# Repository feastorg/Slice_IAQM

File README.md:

# Industrial Air Quality Monitor

Industrial air quality monitor and alarm for BREAD.

## Introduction

[Short introduction on the project.]

## Usage

[Explain how to use the project. Include examples and screenshots if applicable.]

## Documentation

Please refer to the [docs](/docs) for more info.

---

<div align="center">
  
</div>

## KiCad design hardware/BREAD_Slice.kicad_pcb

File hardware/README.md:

## IAQM - Industrial Air Quality Monitor 

## Requirements

### Requirements List

- **Data Logging**
  - Logging of data to SD card
  - Real-time clock for accurate data logging

- **Feedback Alarms**
  - Visual feedback alarm
  - Auditory feedback alarm

- **Air Quality Readings**
  - Ambient temperature sensor
  - Ambient humidity sensor
  - Barometric pressure sensor
  - CO gas sensor
  - CH₄ gas sensor
  - NH₃ gas sensor
  - H₂S gas sensor
  - H₂ gas sensor
  - Smoke / flammable gas sensor
  - VOCs (Volatile Organic Compounds)
    - eCO2 readings
  - AQI (Air Quality Index)

### Component Table

| **Name**            | **Parameters Measured**                                         | **Value Abbreviation** | **Notes**                                                                                  |
|---------------------|-----------------------------------------------------------------|------------------------|-------------------------------------------------------------------------------------------|
| SD Card Reader      | Data Logging                                                    | N/A                    |                                                                                           |
| Real Time Clock     | Global Local Time                                               | N/A                    |                                                                                           |
| Piezo Buzzer        | Auditory Feedback                                               | N/A                    | For Alarm                                                                                      |
| Large LED           | Visual Feedback                                                 | N/A                    | For Alarm                                                                            |
| MQ-7                | Carbon Monoxide                                                 | CO                     | 10～500ppm, needs cycled coil heating.                                                                                |
| MQ-137              | Ammonia Gas                                                     | NH₃                    | 5～500ppm                                                                                  |
| MQ-8                | Hydrogen Gas                                                    | H₂                     | 100～1000ppm                                                                               |
| MQ-136              | Hydrogen Sulfide Gas                                            | H₂S                    | 1～200ppm                                                                                  |
| MQ-2                | Smoke / Combustible Gas                                          | N/A                    | 300～10000ppm (flammable gas)                                                             |
| MQ-3                | Alcohol Gas                                                     | C₂H₅OH                 | 25 ~ 500ppm (alcohol). Detects alcohol gases like a breathalyzer, not added in default build. |
| MQ-4                | Methane CNG Gas                                                 | CH₄                    | 300～10000ppm                                                                              |
| MQ-6                | Liquefied Petroleum Gas (LPG)                                   | C₃H₈                   | 300～10000ppm (propane). Not in default build.                                                                    |
| BME 280             | Ambient Temperature, Relative Humidity, Barometric Pressure     | N/A                    | Ambient Temp. -40 - +85 °C, Rel. Humidity 0 - 100 %, Baro. Pressure 300 - 1100 hPa                                 |
| ENS160              | Total Volatile Organic Compounds, Equivalent Carbon Dioxide, Air Quality Index | TVOC, eCO₂, AQI        | TVOC 0 – 65,000 ppb, eCO2 400 – 65,000ppm (CO₂ equiv.), AQI-UBA 1 to 5 |

### PV Box

| **Name**            | **Parameters Measured**                                         | **Value Abbreviation** | **Notes**                                                                                  |
|---------------------|-----------------------------------------------------------------|------------------------|-------------------------------------------------------------------------------------------|
| SD Card Reader      | Data Logging                                                    | N/A                    |                                                                                           |
| Real Time Clock     | Global Local Time                                               | N/A                    |                                                                                           |
| Piezo Buzzer        | Auditory Feedback                                               | N/A                    | For Alarm                                                                                      |
| Large LED           | Visual Feedback                                                 | N/A                    | For Alarm                                                                            |
| MQ-7                | Carbon Monoxide                                                 | CO                     | 10～500ppm, needs cycled coil heating.                                                                                |
| MQ-137              | Ammonia Gas                                                     | NH₃                    | 5～500ppm                                                                                  |
| MQ-8                | Hydrogen Gas                                                    | H₂                     | 100～1000ppm                                                                               |
| MQ-136              | Hydrogen Sulfide Gas                                            | H₂S                    | 1～200ppm                                                                                  |
| MQ-4                | Methane CNG Gas                                                 | CH₄                    | 300～10000ppm                                                                              |
| MQ-9B                | Carbon Monoxide & Methane CNG Gas                                                 | CO & CH₄                    | 10～500ppm CO, 300～10000ppm CH4                                                                              |
| BME 280             | Ambient Temperature, Relative Humidity, Barometric Pressure     | N/A                    | Ambient Temp. -40 - +85 °C, Rel. Humidity 0 - 100 %, Baro. Pressure 300 - 1100 hPa                                 |
| ENS160              | Total Volatile Organic Compounds, Equivalent Carbon Dioxide, Air Quality Index | TVOC, eCO₂, AQI        | TVOC 0 – 65,000 ppb, eCO2 400 – 65,000ppm (CO₂ equiv.), AQI-UBA 1 to 5 |

### Parts List

- SD conn: https://www.mouser.ca/ProductDetail/Molex/502570-0893?qs=xbccQsLEe0eiL%252BVgS3E4nA%3D%3D
- SD level shifter: https://www.mouser.ca/ProductDetail/Texas-Instruments/TXB0104D?qs=oFXvjAmG9Eh0u9dpGkn5zg%3D%3D
- batt holder: https://www.mouser.ca/ProductDetail/Keystone-Electronics/3000?qs=Mn60vILZNNbcLh3ZnzbtUw%3D%3D

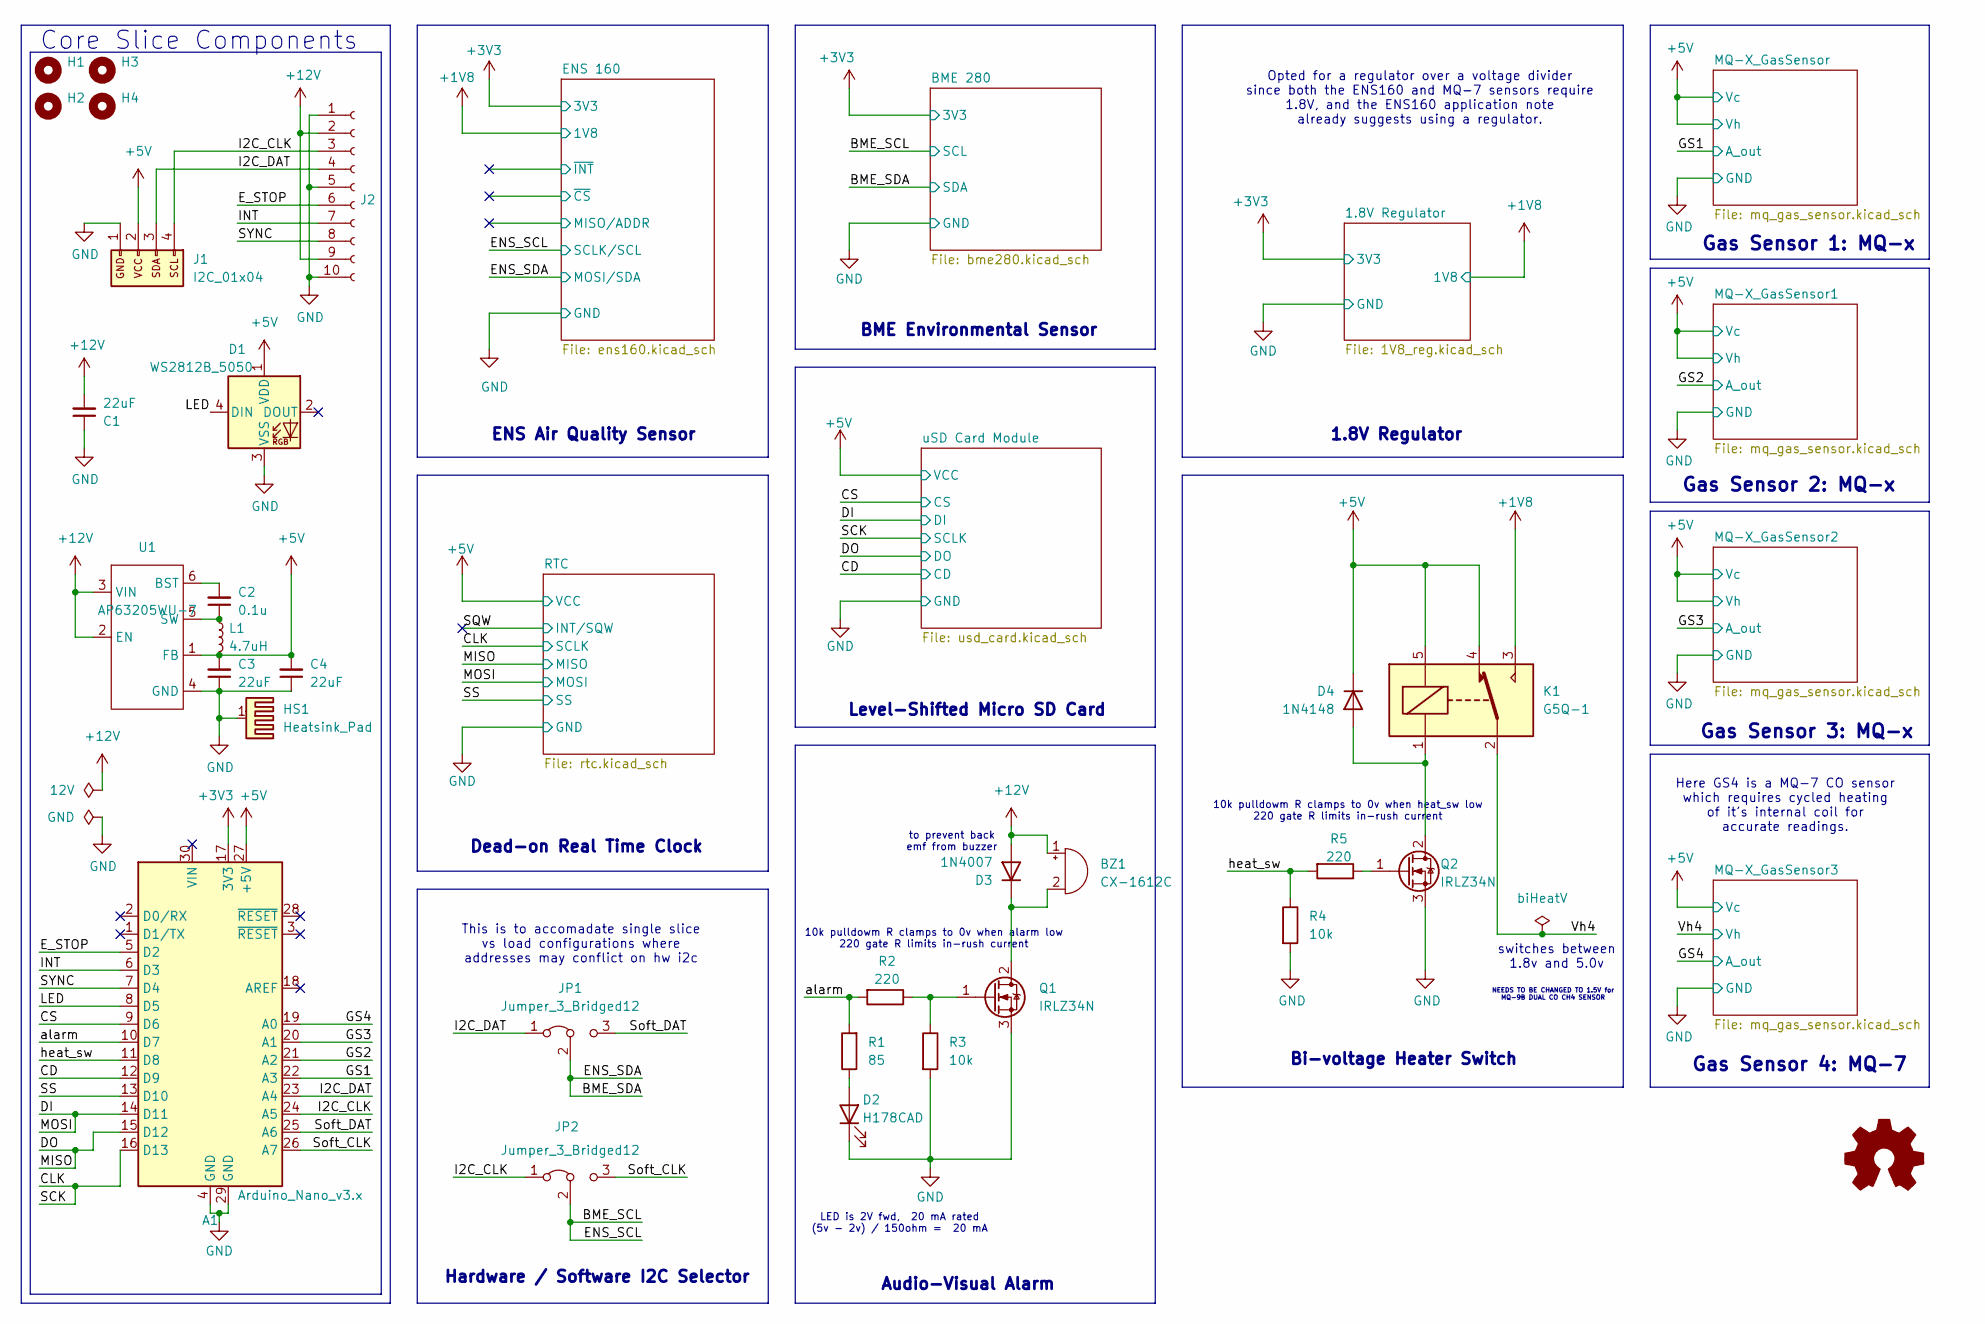
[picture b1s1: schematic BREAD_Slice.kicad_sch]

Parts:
A1: Arduino_Nano_v3.x; Arduino_Nano
BZ1: CX-1612C; Buzzer_15x7.5RM7.6
C1, C3, C4: 22uF; C_1206_3216Metric
C2: 0.1u; C_1206_3216Metric
D1: WS2812B_5050; WS2812-5050-4PIN
D2: H178CAD; H178CAD_P2.54mm_RightAngle_LED
D3: 1N4007; D_DO-35_SOD27_P7.62mm_Horizontal
D4: 1N4148; D_DO-35_SOD27_P7.62mm_Horizontal
H1, H2, H3, H4: MountingHole; MountingHole_5mm
HS1: Heatsink_Pad; Thermal_Pad
J1: I2C_01x04; JST_SH_SM04B-SRSS-TB_1x04-1MP_P1.00mm_Horizontal
J2: Conn_01x10_Female; PinSocket_1x10_P2.54mm_Horizontal
JP1, JP2: Jumper_3_Bridged12; SolderJumper-3_P1.3mm_Bridged2Bar12_Pad1.0x1.5mm_NumberLabe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
K1: G5Q-1; Relay_SPDT_Omron-G5Q-1
L1: 4.7uH; L_1210_3225Metric
Q1, Q2: IRLZ34N; TO-220-3_Horizontal_TabDown
R1: 85; R_1206_3216Metric_Pad1.30x1.75mm_HandSolder
R2, R5: 220; R_1206_3216Metric_Pad1.30x1.75mm_HandSolder
R3, R4: 10k; R_1206_3216Metric_Pad1.30x1.75mm_HandSolder
U1: AP63205WU-7; TSOT-23-6

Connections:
+1V8: K1.3; also elsewhere on the board
+3V3: A1.17 (3V3); also elsewhere on the board
+5V: A1.27 (+5V), C3.2, C4.2, D1.1 (VDD), D4.1 (K), J1.2, K1.4, K1.5, L1.2, U1.1 (FB); also elsewhere on the board
+12V: BZ1.1 (+), C1.2, D3.2 (A), J2.2, J2.9, U1.2 (EN), U1.3 (VIN)
/BME_SCL: JP2.2 (C); also elsewhere on the board
/BME_SDA: JP1.2 (C); also elsewhere on the board
/CD: A1.12 (D9); also elsewhere on the board
/CLK: A1.16 (D13); also elsewhere on the board
/CS: A1.9 (D6); also elsewhere on the board
/DI: A1.14 (D11); also elsewhere on the board
/DO: A1.15 (D12); also elsewhere on the board
/E_STOP: A1.5 (D2), J2.6
/GS1: A1.22 (A3); also elsewhere on the board
/GS2: A1.21 (A2); also elsewhere on the board
/GS3: A1.20 (A1); also elsewhere on the board
/GS4: A1.19 (A0); also elsewhere on the board
/I2C_CLK: A1.24 (A5), J1.4, J2.3, JP2.1 (A)
/I2C_DAT: A1.23 (A4), J1.3, J2.4, JP1.1 (A)
/INT: A1.6 (D3), J2.7
/LED: A1.8 (D5), D1.4 (DIN)
/SS: A1.13 (D10); also elsewhere on the board
/SYNC: A1.7 (D4), J2.8
/Soft_CLK: A1.26 (A7), JP2.3 (B)
/Soft_DAT: A1.25 (A6), JP1.3 (B)
/Vh4: K1.2; also elsewhere on the board
/alarm: A1.10 (D7), R1.2, R2.2
/heat_sw: A1.11 (D8), R4.1, R5.2
GND: A1.4 (GND), A1.29 (GND), C1.1, C3.1, C4.1, D1.3 (VSS), D2.1 (K), HS1.1, J1.1, J2.1, J2.5, J2.10, Q1.3 (S), Q2.3 (S), R3.2, R4.2, U1.4 (GND); also elsewhere on the board
unnamed: BZ1.2 (-), D3.1 (K), Q1.2 (D)
unnamed: D2.2 (A), R1.1
unnamed: D4.2 (A), K1.1, Q2.2 (D)
unnamed: Q1.1 (G), R2.1, R3.1
unnamed: Q2.1 (G), R5.1
unnamed: C2.2, U1.6 (BST)
unnamed: C2.1, L1.1, U1.5 (SW)

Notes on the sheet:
Gas Sensor 2: MQ-x
NEEDS TO BE CHANGED TO 1.5V for MQ-9B DUAL CO CH4 SENSOR
LED is 2V fwd, 20 mA rated (5v - 2v) / 150ohm = 20 mA
Gas Sensor 1: MQ-x
Bi-voltage Heater Switch
Gas Sensor 4: MQ-7
Gas Sensor 3: MQ-x
switches between 1.8v and 5.0v
1.8V Regulator
Level-Shifted Micro SD Card
Audio-Visual Alarm
Core Slice Components
BME Environmental Sensor
10k pulldowm R clamps to 0v when heat_sw low 220 gate R limits in-rush current
to prevent back emf from buzzer
10k pulldowm R clamps to 0v when alarm low 220 gate R limits in-rush current
Opted for a regulator over a voltage divider since both the ENS160 and MQ-7 sensors require 1.8V, and the ENS160 application note already suggests using a regulator.
ENS Air Quality Sensor
Dead-on Real Time Clock
This is to accomadate single slice vs load configurations where addresses may conflict on hw i2c
Here GS4 is a MQ-7 CO sensor which requires cycled heating of it's internal coil for accurate readings.
Hardware / Software I2C Selector

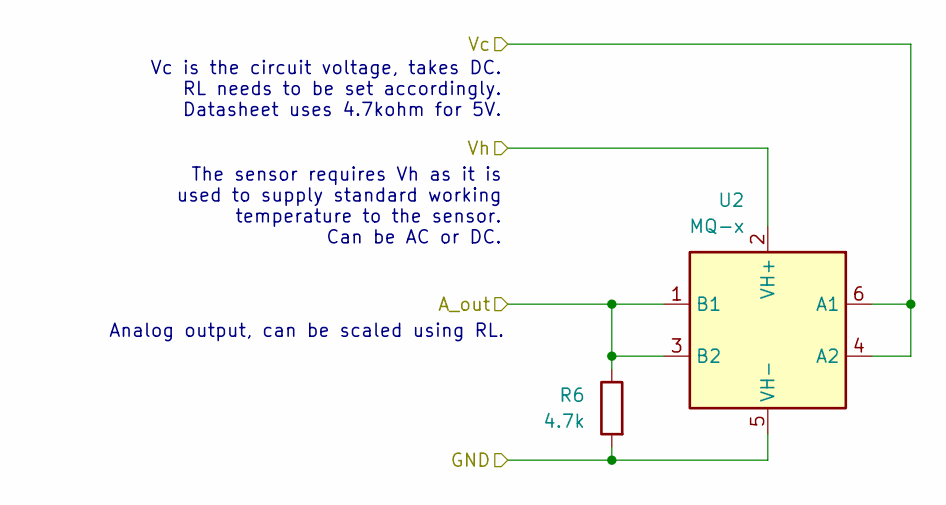
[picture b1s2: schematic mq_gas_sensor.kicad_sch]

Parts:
R6: 4.7k; R_1206_3216Metric_Pad1.30x1.75mm_HandSolder
U2: MQ-x; MQ-6

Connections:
+5V: U2.2 (VH+), U2.4 (A2), U2.6 (A1); also elsewhere on the board
/GS1: R6.1, U2.1 (B1), U2.3 (B2); also elsewhere on the board
GND: R6.2, U2.5 (VH-); also elsewhere on the board

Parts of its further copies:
R7, R8, R9: 4.7k; R_1206_3216Metric_Pad1.30x1.75mm_HandSolder
U3, U4, U5: MQ-x; MQ-6

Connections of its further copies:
+5V: U3.2 (VH+), U3.4 (A2), U3.6 (A1), U4.2 (VH+), U4.4 (A2), U4.6 (A1), U5.4 (A2), U5.6 (A1); also elsewhere on the board
/GS2: R7.1, U3.1 (B1), U3.3 (B2); also elsewhere on the board
/GS3: R8.1, U4.1 (B1), U4.3 (B2); also elsewhere on the board
/GS4: R9.1, U5.1 (B1), U5.3 (B2); also elsewhere on the board
/Vh4: U5.2 (VH+); also elsewhere on the board
GND: R7.2, R8.2, R9.2, U3.5 (VH-), U4.5 (VH-), U5.5 (VH-); also elsewhere on the board

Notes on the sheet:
The sensor requires Vh as it is used to supply standard working temperature to the sensor. Can be AC or DC.
Analog output, can be scaled using RL.
Vc is the circuit voltage, takes DC. RL needs to be set accordingly. Datasheet uses 4.7kohm for 5V.

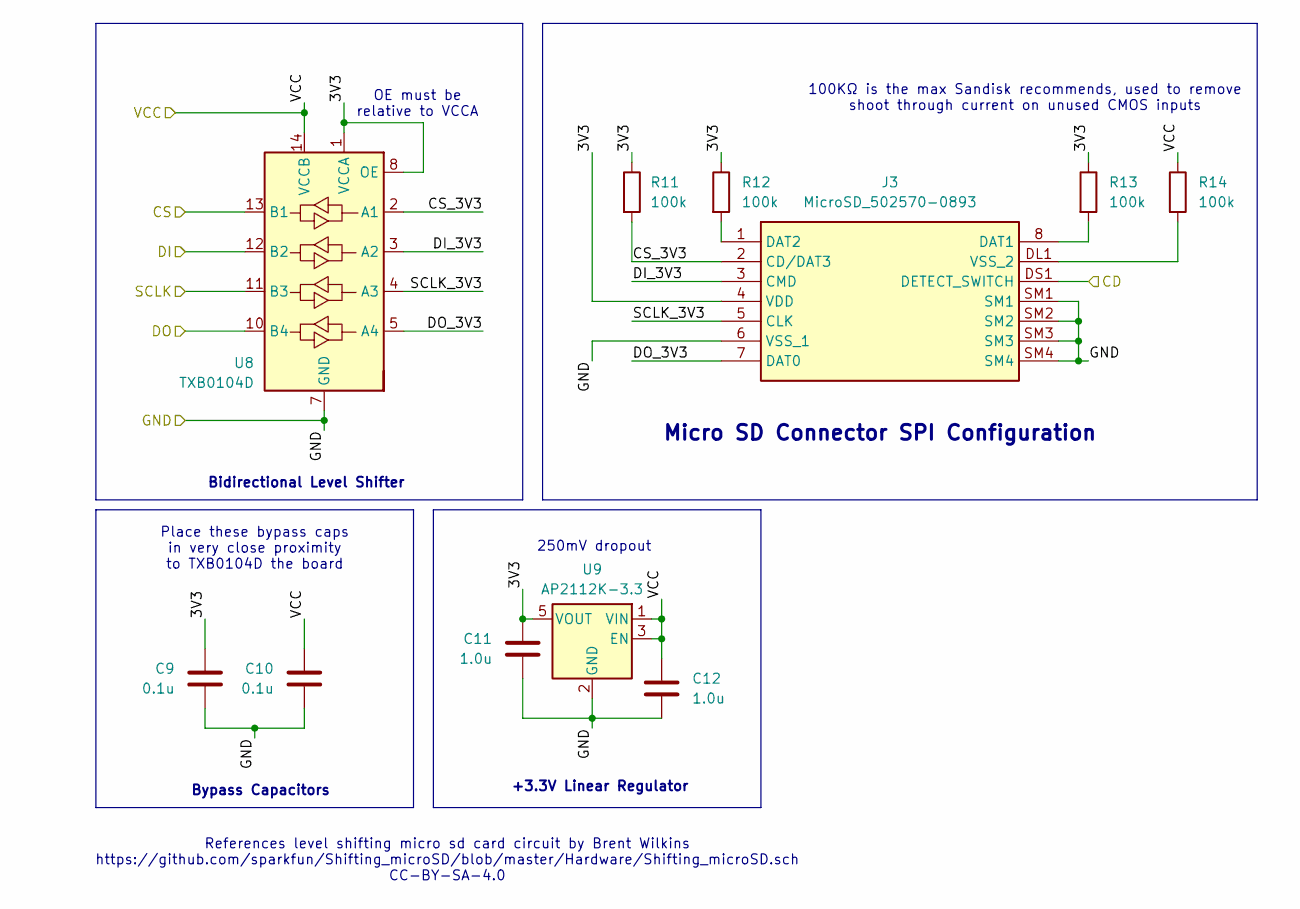
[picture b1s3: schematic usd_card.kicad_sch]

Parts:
C9, C10: 0.1u; C_1206_3216Metric_Pad1.33x1.80mm_HandSolder
C11, C12: 1.0u; C_1206_3216Metric_Pad1.33x1.80mm_HandSolder
J3: MicroSD_502570-0893; MicroSD_5025700893; Mouser Part Number 538-502570-0893
R11, R12, R13, R14: 100k; R_1206_3216Metric_Pad1.30x1.75mm_HandSolder
U8: TXB0104D; SOIC-14_3.9x8.7mm_P1.27mm
U9: AP2112K-3.3; SOT-23-5

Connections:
+5V: C10.1, C12.1, R14.1, U8.14 (VCCB), U9.1 (VIN), U9.3 (EN); also elsewhere on the board
/CD: J3.DS1 (DETECT_SWITCH); also elsewhere on the board
/CLK: U8.11 (B3); also elsewhere on the board
/CS: U8.13 (B1); also elsewhere on the board
/DI: U8.12 (B2); also elsewhere on the board
/DO: U8.10 (B4); also elsewhere on the board
/uSD Card Module/3V3: C9.1, C11.1, J3.4 (VDD), R11.1, R12.1, R13.1, U8.1 (VCCA), U8.8 (OE), U9.5 (VOUT)
/uSD Card Module/CS_3V3: J3.2 (CD/DAT3), R11.2, U8.2 (A1)
/uSD Card Module/DI_3V3: J3.3 (CMD), U8.3 (A2)
/uSD Card Module/DO_3V3: J3.7 (DAT0), U8.5 (A4)
/uSD Card Module/SCLK_3V3: J3.5 (CLK), U8.4 (A3)
GND: C9.2, C10.2, C11.2, C12.2, J3.6 (VSS_1), J3.SM1, J3.SM2, J3.SM3, J3.SM4, U8.7 (GND), U9.2 (GND); also elsewhere on the board
unnamed: J3.8 (DAT1), R13.2
unnamed: J3.1 (DAT2), R12.2
unnamed: J3.DL1 (VSS_2), R14.2

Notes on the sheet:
Bidirectional Level Shifter
Place these bypass caps in very close proximity to TXB0104D the board
+3.3V Linear Regulator
Micro SD Connector SPI Configuration
OE must be relative to VCCA
Bypass Capacitors
References level shifting micro sd card circuit by Brent Wilkins https://github.com/sparkfun/Shifting_microSD/blob/master/Hardware/Shifting_microSD.sch CC-BY-SA-4.0
100KΩ is the max Sandisk recommends, used to remove shoot through current on unused CMOS inputs
250mV dropout

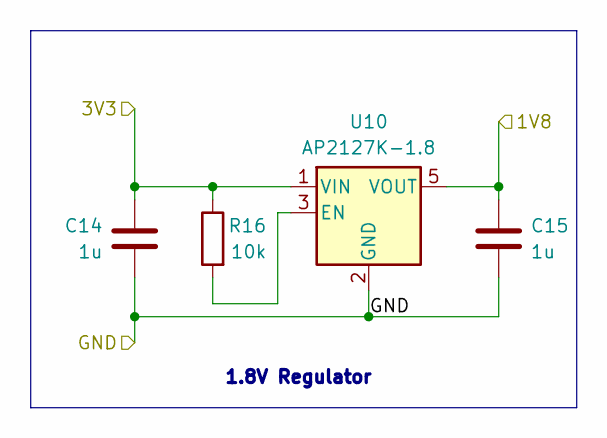
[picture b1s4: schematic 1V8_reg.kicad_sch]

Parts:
C14, C15: 1u; C_1206_3216Metric_Pad1.33x1.80mm_HandSolder
R16: 10k; R_1206_3216Metric_Pad1.30x1.75mm_HandSolder
U10: AP2127K-1.8; SOT-23-5

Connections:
+1V8: C15.1, U10.5 (VOUT); also elsewhere on the board
+3V3: C14.1, R16.1, U10.1 (VIN); also elsewhere on the board
GND: C14.2, C15.2, U10.2 (GND); also elsewhere on the board
unnamed: R16.2, U10.3 (EN)

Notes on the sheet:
1.8V Regulator

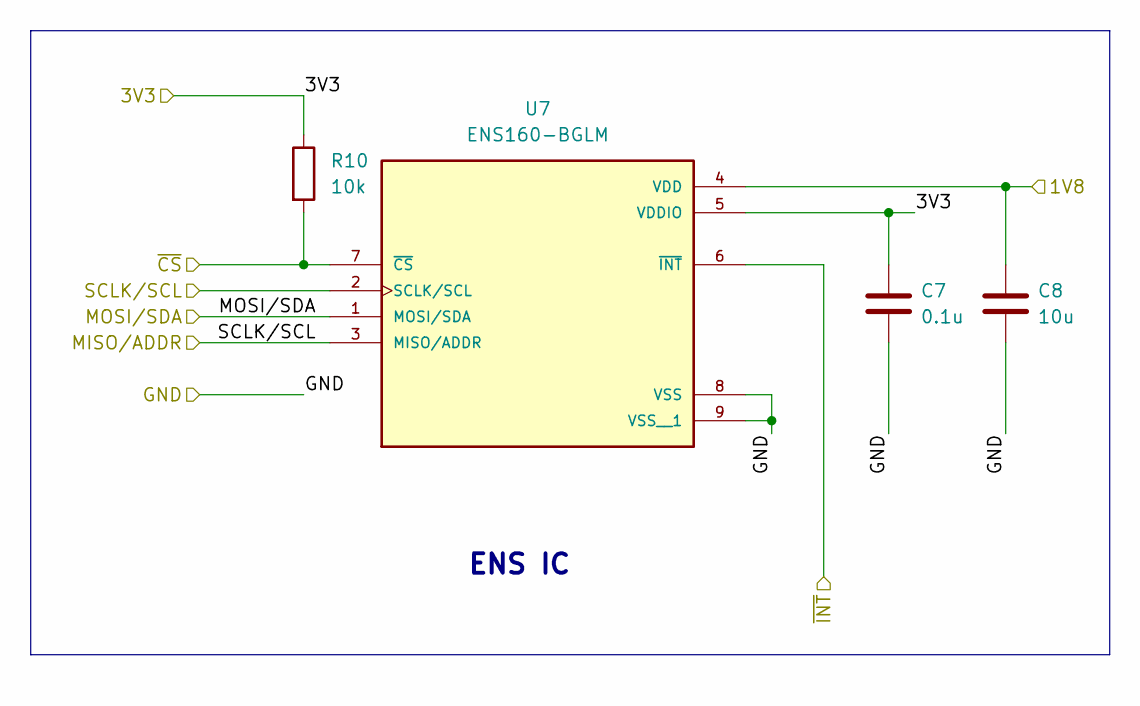
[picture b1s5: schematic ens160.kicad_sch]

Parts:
C7: 0.1u; C_1206_3216Metric_Pad1.33x1.80mm_HandSolder
C8: 10u; C_1206_3216Metric_Pad1.33x1.80mm_HandSolder
R10: 10k; R_1206_3216Metric_Pad1.30x1.75mm_HandSolder
U7: ENS160-BGLM; XDCR_ENS160-BGLM; PARTREV 1.3

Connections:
+1V8: C8.1, U7.4 (VDD); also elsewhere on the board
+3V3: C7.1, R10.1, U7.5 (VDDIO); also elsewhere on the board
/BME_SCL: U7.2 (SCLK/SCL), U7.3 (MISO/ADDR); also elsewhere on the board
/BME_SDA: U7.1 (MOSI/SDA); also elsewhere on the board
/ENS 160/~CS: R10.2, U7.7 (~CS)
/ENS 160/~INT: U7.6 (~INT)
GND: C7.2, C8.2, U7.8 (VSS), U7.9 (VSS__1); also elsewhere on the board

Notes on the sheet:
ENS IC

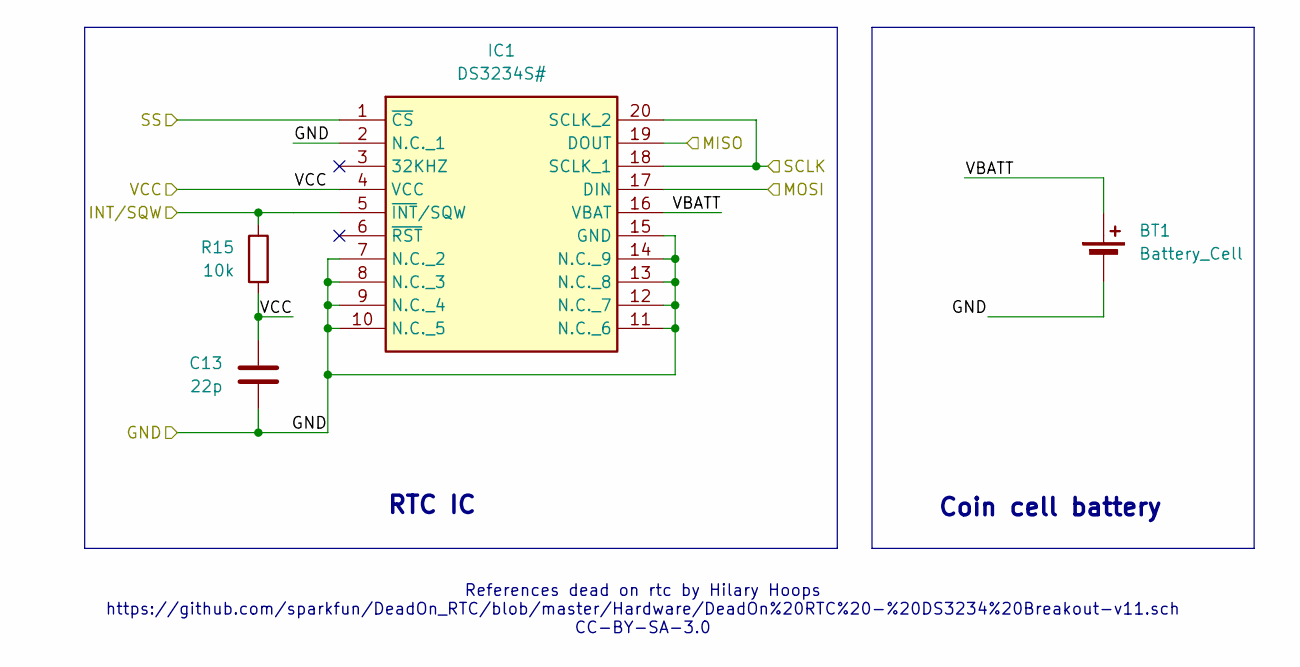
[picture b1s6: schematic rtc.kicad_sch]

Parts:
BT1: Battery_Cell; BatteryHolder_Keystone_3000_1x12mm
C13: 22p; C_1206_3216Metric_Pad1.33x1.80mm_HandSolder
IC1: DS3234S#; SOIC127P1032X265-20N; Mouser Part Number 700-DS3234S#
R15: 10k; R_1206_3216Metric_Pad1.30x1.75mm_HandSolder

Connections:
+5V: C13.1, IC1.4 (VCC), R15.2; also elsewhere on the board
/CLK: IC1.18 (SCLK_1), IC1.20 (SCLK_2); also elsewhere on the board
/DI: IC1.17 (DIN); also elsewhere on the board
/DO: IC1.19 (DOUT); also elsewhere on the board
/RTC/VBATT: BT1.1 (+), IC1.16 (VBAT)
/SQW: IC1.5 (~INT/SQW), R15.1
/SS: IC1.1 (~CS); also elsewhere on the board
GND: BT1.2 (-), C13.2, IC1.2 (N.C._1), IC1.7 (N.C._2), IC1.8 (N.C._3), IC1.9 (N.C._4), IC1.10 (N.C._5), IC1.11 (N.C._6), IC1.12 (N.C._7), IC1.13 (N.C._8), IC1.14 (N.C._9), IC1.15 (GND); also elsewhere on the board

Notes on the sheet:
References dead on rtc by Hilary Hoops https://github.com/sparkfun/DeadOn_RTC/blob/master/Hardware/DeadOn%20RTC%20-%20DS3234%20Breakout-v11.sch CC-BY-SA-3.0
RTC IC
Coin cell battery

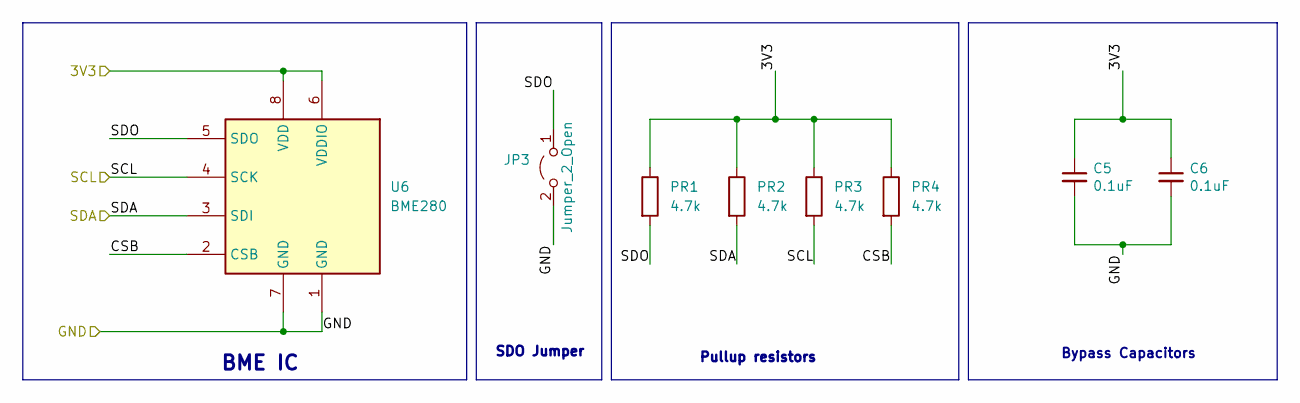
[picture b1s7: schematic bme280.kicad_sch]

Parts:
C5, C6: 0.1uF; C_0805_2012Metric
JP3: Jumper_2_Open; SolderJumper-2_P1.3mm_Open_TrianglePad1.0x1.5mm
PR1, PR2, PR3, PR4: 4.7k; R_1206_3216Metric_Pad1.30x1.75mm_HandSolder
U6: BME280; Bosch_LGA-8_2.5x2.5mm_P0.65mm_ClockwisePinNumbering

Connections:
+3V3: C5.1, C6.1, PR1.1, PR2.1, PR3.1, PR4.1, U6.6 (VDDIO), U6.8 (VDD); also elsewhere on the board
/BME 280/CSB: PR4.2, U6.2 (CSB)
/BME 280/SDO: JP3.1 (A), PR1.2, U6.5 (SDO)
/BME_SCL: PR3.2, U6.4 (SCK); also elsewhere on the board
/BME_SDA: PR2.2, U6.3 (SDI); also elsewhere on the board
GND: C5.2, C6.2, JP3.2 (B), U6.1 (GND), U6.7 (GND); also elsewhere on the board

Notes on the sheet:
Bypass Capacitors
SDO Jumper
BME IC
Pullup resistors

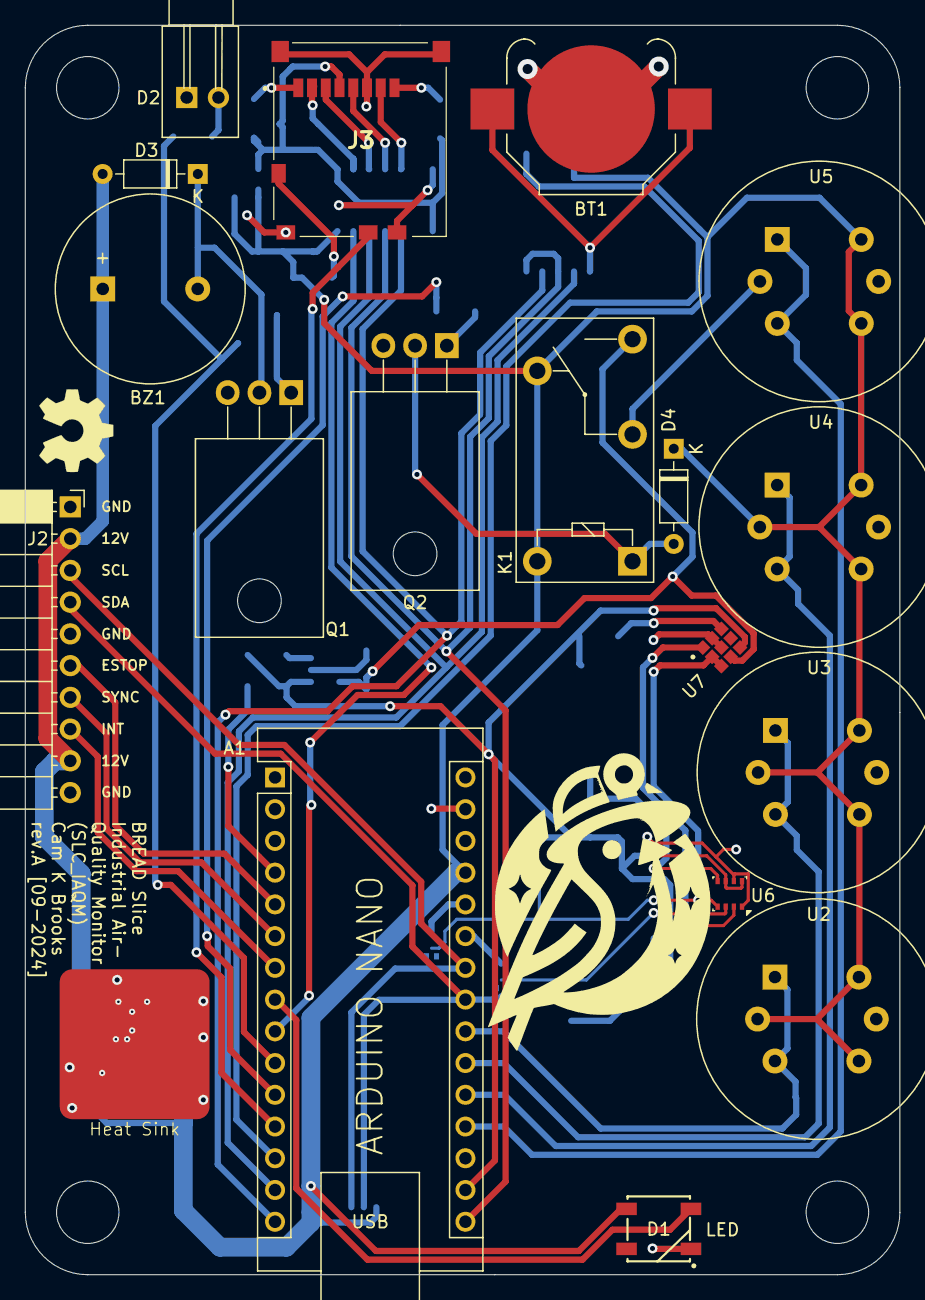
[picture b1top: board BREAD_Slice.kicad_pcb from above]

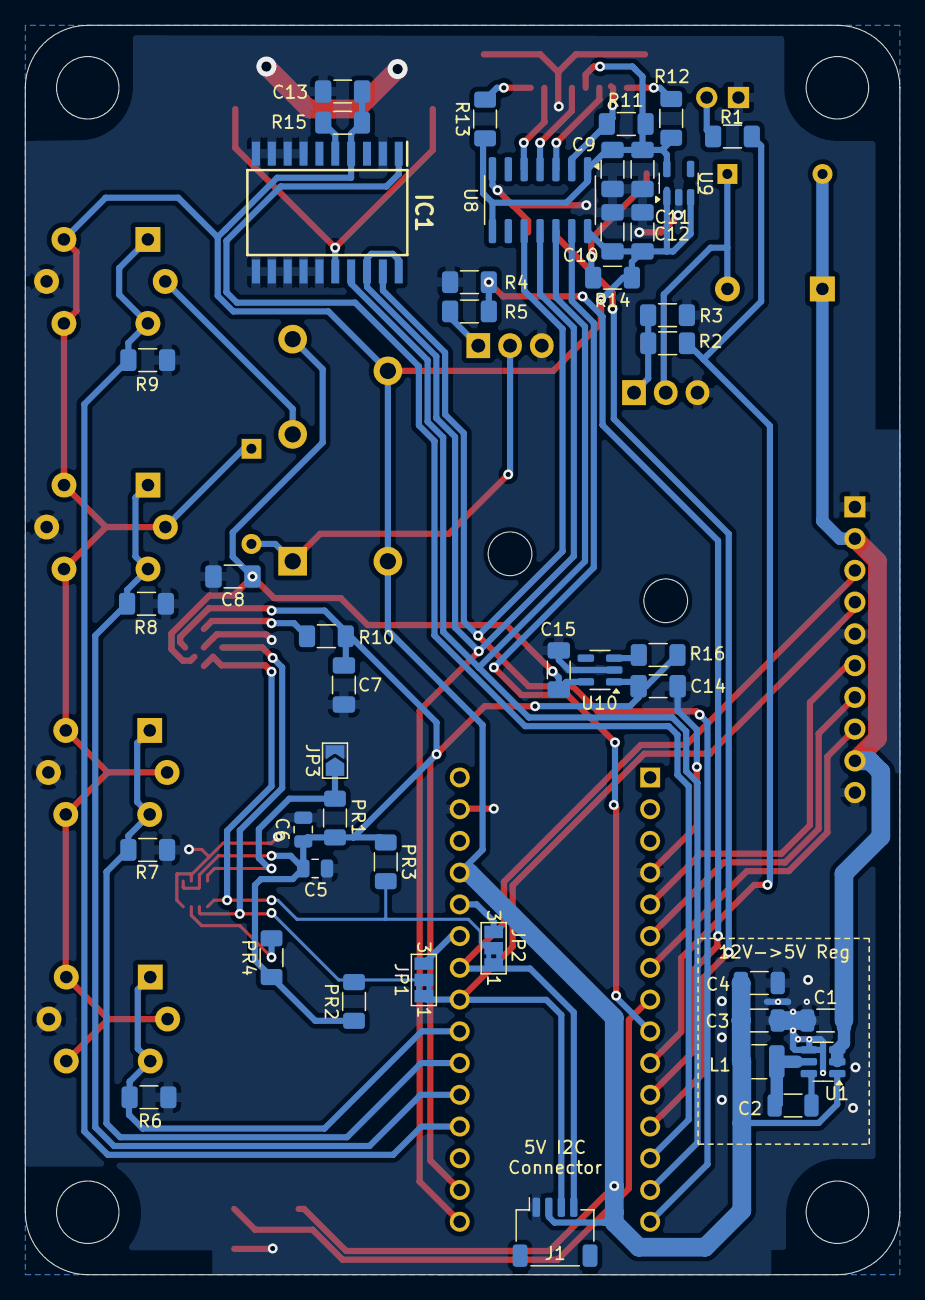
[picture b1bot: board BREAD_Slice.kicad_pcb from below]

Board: 2 copper layers, 70.0 x 100.0 mm, 69 parts (45 on the bottom side), 49 nets.

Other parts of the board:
Logo1: Logo_Open_Hardware_Small; OSHW-Symbol_6.7x6mm_SilkScreen

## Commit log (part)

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2024-08-30 completed requirements and conceptual design, added gas sensors part of schematic for detailed design
2024-09-06 completed schematic
2024-09-08 organized schem and updated readme
2024-09-09 completed board
2024-09-10 set repo
2024-09-19 added product links to bom
2024-09-19 updated parts list and swapped relay to omron var
2024-09-24 local push
2024-09-24 checked output for order
2024-09-30 JLCPCB order rev-A
2024-10-25 final touches for order and assembly
2026-05-20 Add slice.yaml manifest (schema v1.0)
2026-05-24 Add KiBot/docs pipeline
2026-05-24 📄 KiBot index + board renders (auto)
2026-05-24 TODO: all CI green
